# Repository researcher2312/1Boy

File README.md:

# 1Boy

Project made mainly for fun, but also for microcontroller project on university.
## Hardware
Credit card-sized 'console' based on ATtiny2313 with 1-dimensional screen, two buttons and power switch. 4 leds on the left and on the right are just green, while the middle one is RGB.
Powered by single CR2032 battery.

## Games
**Lowest cost console on market, up to four fun games!**
*Due to lack of memory, currently two games can be played:*

- Pong (1P/2P) - bounce the ball between you and other player or play a duel between your left and right hand
- Memory (1P) - repeat the lengthening sequence of lights

Planned games (after optimalisation of first two):

- Cowboys (2P) - be the fastest hand in the west and press the button faster than the other player after the countdown
- Space shooter (1P) - defeat aliens by pressing buttons in set pattern for each rgb colour

board files created in Cadsoft Eagle

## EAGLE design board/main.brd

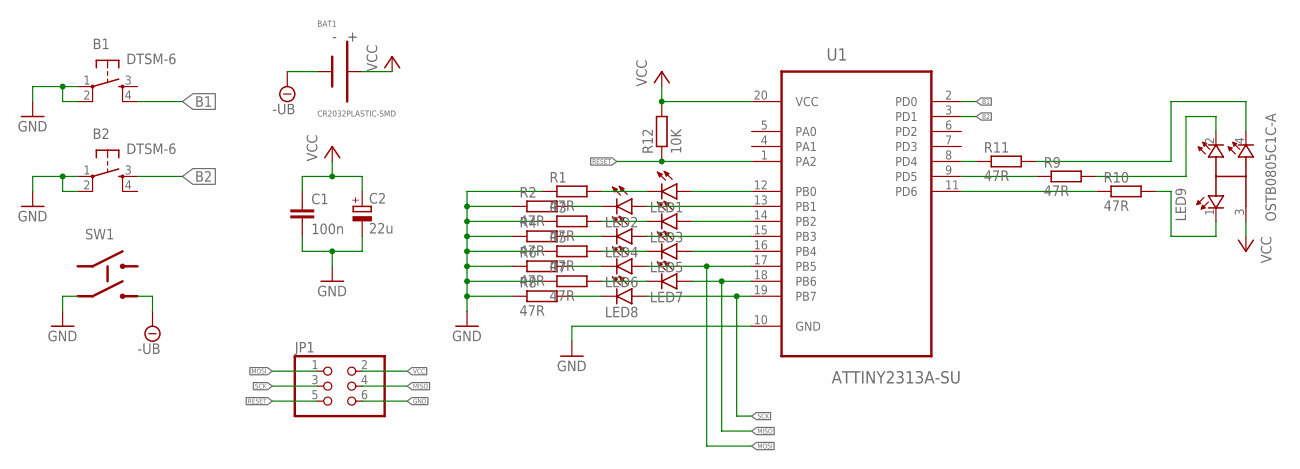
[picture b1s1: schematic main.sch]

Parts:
B1, B2: DTSM-6
BAT1: CR2032PLASTIC-SMD; BIG-SMD
C1: 100n; C0805
C2: 22u; SMC_A
JP1: PINHD-2X3; 2X03
LED1, LED2, LED3, LED4, LED5, LED6, LED7, LED8: LEDCHIP-LED0805; CHIP-LED0805
LED9: OSTB0805C1C-A; LEDSC200X125X110-4N
R1, R2, R3, R4, R5, R6, R7, R8, R9, R10, R11: 47R; R0805
R12: 10K; R0805
SW1: MSS-22D18; 22D18
U1: ATTINY2313A-SU; SOIC127P1032X265-20N

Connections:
-UB: BAT1.1 (MIN), SW1.6 (OUT2)
B1: B1.4, U1.2 (PD0)
B2: B2.3, U1.3 (PD1)
GND: B1.1, B1.2, B2.1, B2.2, C1.2, C2.-, JP1.6, R1.1, R2.1, R3.1, R4.1, R5.1, R6.1, R7.1, R8.1, SW1.5 (IN2), U1.10 (GND)
MISO: JP1.4, LED7.A, U1.18 (PB6)
MOSI: JP1.1, LED6.A, U1.17 (PB5)
unnamed: LED1.A, U1.12 (PB0)
unnamed: LED1.C, R1.2
unnamed: LED2.A, U1.13 (PB1)
unnamed: LED2.C, R2.2
unnamed: LED3.A, U1.14 (PB2)
unnamed: LED3.C, R3.2
unnamed: LED4.A, U1.15 (PB3)
unnamed: LED4.C, R4.2
unnamed: LED5.A, U1.16 (PB4)
unnamed: LED5.C, R5.2
unnamed: LED6.C, R6.2
unnamed: LED7.C, R7.2
unnamed: LED8.C, R8.2
unnamed: R11.1, U1.8 (PD4)
unnamed: R9.1, U1.9 (PD5)
unnamed: R10.1, U1.11 (PD6)
unnamed: LED9.1, R10.2
unnamed: LED9.2, R9.2
unnamed: LED9.4, R11.2
RESET: JP1.5, R12.1, U1.1 (PA2)
SCK: JP1.3, LED8.A, U1.19 (PB7)
VCC: BAT1.2 (PLUS), C1.1, C2.+, JP1.2, LED9.3, R12.2, U1.20 (VCC)

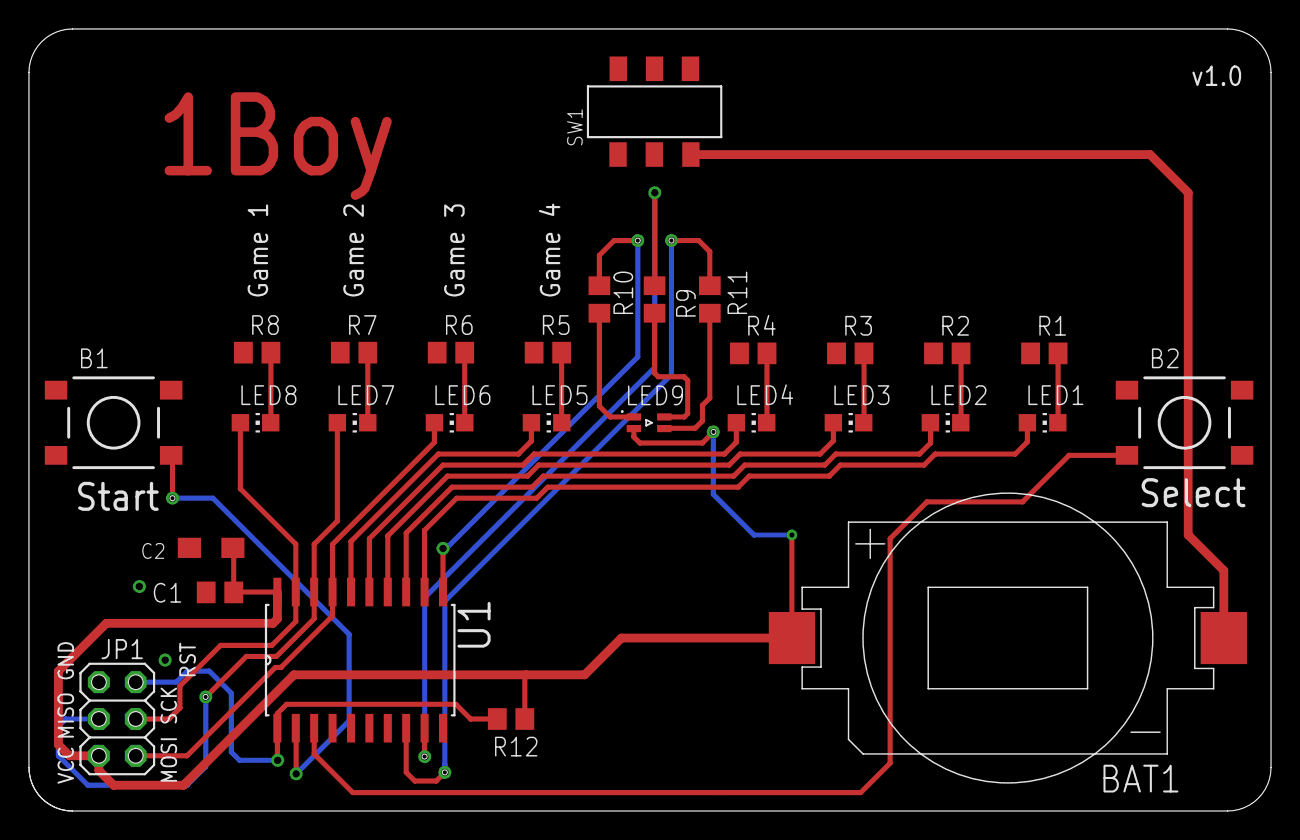
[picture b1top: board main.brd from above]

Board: 2 copper layers, 85.7 x 54.0 mm, 29 parts (0 on the bottom side), 28 nets.

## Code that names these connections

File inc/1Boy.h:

/*
 * 1Boy.h
 *
 *  Created on: 30 gru 2019
 *      Author: researcher
 */

#ifndef INC_1BOY_H_
#define INC_1BOY_H_

#define LED1 (1<<PB7)
#define LED2 (1<<PB6)
#define LED3 (1<<PB5)
#define LED4 (1<<PB4)
#define LED5 (1<<PB3)
#define LED6 (1<<PB2)
#define LED7 (1<<PB1)
#define LED8 (1<<PB0)

#define LED_RD (1<<PD6)
#define LED_GR (1<<PD5)
#define LED_BL (1<<PD4)

#define LED_RD_OFF PORTD |= LED_RD
#define LED_GR_OFF PORTD |= LED_GR
#define LED_BL_OFF PORTD |= LED_BL

#define LED_RD_ON PORTD &= ~LED_RD
#define LED_GR_ON PORTD &= ~LED_GR
#define LED_BL_ON PORTD &= ~LED_BL

#define BT1 (1<<PD0)
#define BT2 (1<<PD1)

#define BT1_DOWN !(PIND & BT1)
#define BT2_DOWN !(PIND & BT2)

uint8_t pressedNow(uint8_t button_number);

extern uint16_t delay;
extern volatile unsigned int time_ms;

#endif /* INC_1BOY_H_ */

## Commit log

2020-01-11 configured the timer and interrupts
2020-01-11 changed frequency of interrupt to 1KHz
2020-01-11 added button pressing
2020-01-11 added driver for basic screen operations
2020-01-21 added screen functions for points, lines and full green
2020-01-21 added first game and button state functions
2020-01-21 added blink function to display
2020-01-21 added finish for the frst game
2020-01-28 polished blink function and moved pressing function definition into 1Boy.h
2020-01-28 added game selection stage
2020-01-28 moved the football game into separate file
2020-01-29 added a welcome sequence
2020-01-29 added new game - memory
2020-01-29 bugs fixed
2020-03-03 added board files
